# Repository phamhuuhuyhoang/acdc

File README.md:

# acdc

Power electronics toolbox

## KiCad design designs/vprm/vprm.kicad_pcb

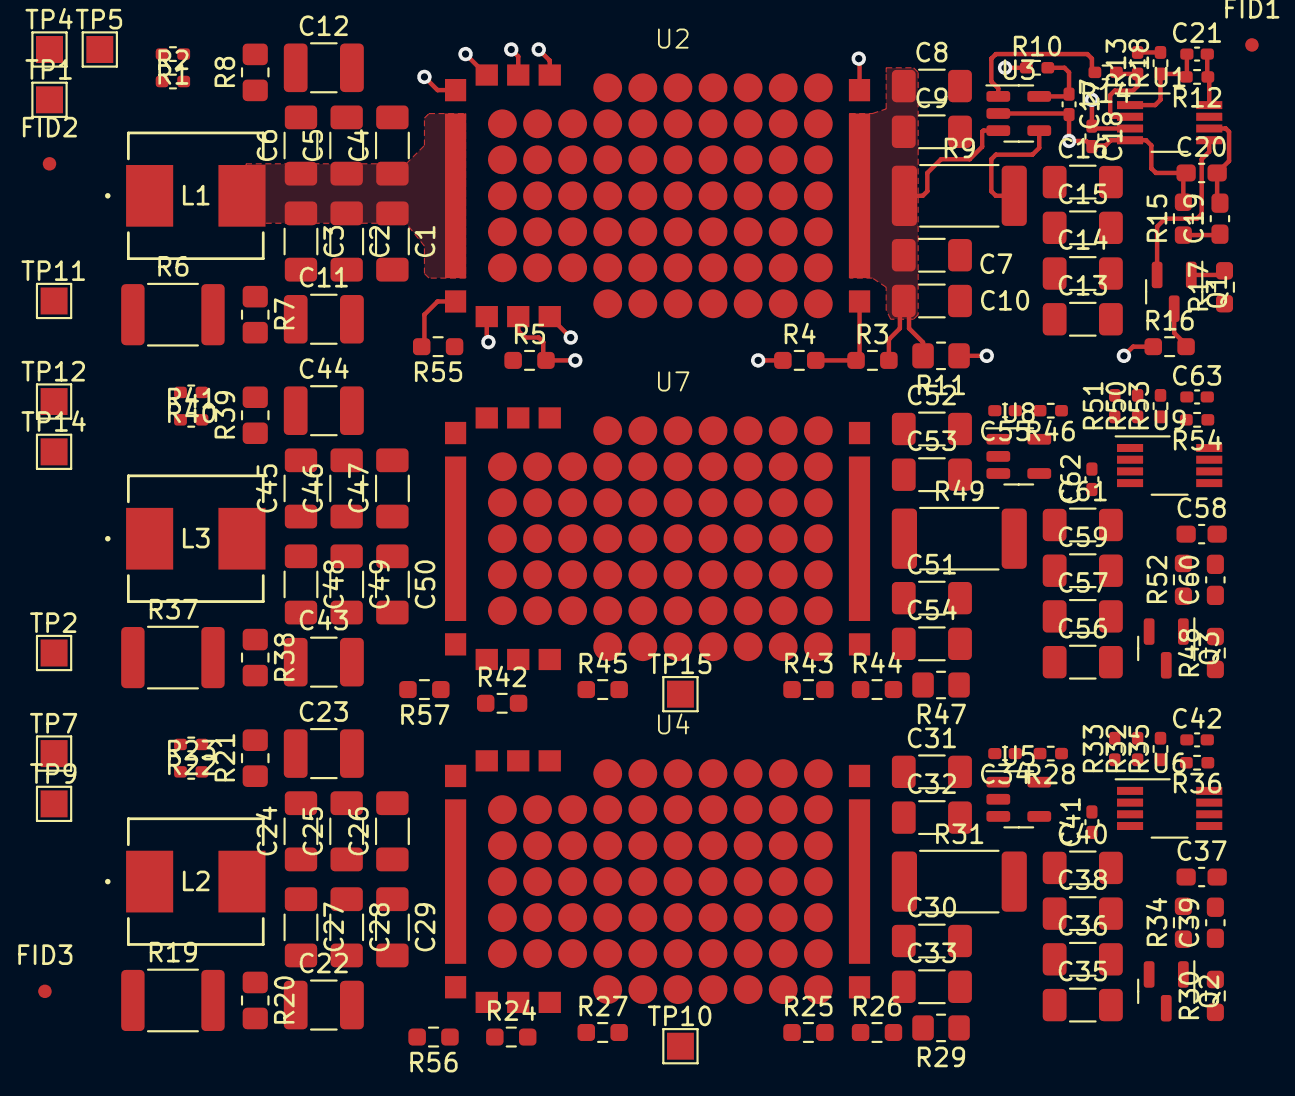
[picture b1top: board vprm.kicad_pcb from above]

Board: 8 copper layers, 150 parts (1 on the bottom side), 80 nets.

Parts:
C1, C2, C3, C4, C5, C6, C24, C25, C26, C27, C28, C29, C45, C46, C47, C48, C49, C50: C; C_1206_3216Metric_Pad1.33x1.80mm_HandSolder
C7, C8, C9, C10, C13, C14, C15, C16, C30, C31, C32, C33, C35, C36, C38, C40, C51, C52, C53, C54, C56, C57, C59, C61: 4.7uF; C_1206_3216Metric_Pad1.33x1.80mm_HandSolder
C11, C12, C22, C23, C43, C44: C; C_1210_3225Metric_Pad1.33x2.70mm_HandSolder
C17, C18, C21, C34, C41, C42, C55, C62, C63: 0.1uF; C_0402_1005Metric_Pad0.74x0.62mm_HandSolder
C19, C20, C37, C39, C58, C60: 0.1uF; C_0603_1608Metric_Pad1.08x0.95mm_HandSolder
FID1, FID2, FID3: Fiducial; Fiducial_0.75mm_Mask1.5mm
L1, L2, L3: L; IND_IHLP_2525_CZ_VIS-M
Q1, Q2, Q3: BC846; SOT-23
R1, R2, R22, R23, R40, R41: R; R_0402_1005Metric_Pad0.72x0.64mm_HandSolder
R3, R4, R5, R15, R16, R24, R25, R26, R27, R34, R42, R43, R44, R45, R52, R55, R56, R57: R; R_0603_1608Metric_Pad0.98x0.95mm_HandSolder
R6, R19, R37: R_US; R_1812_4532Metric_Pad1.30x3.40mm_HandSolder
R7, R8, R20, R21, R38, R39: R_US; R_0805_2012Metric_Pad1.20x1.40mm_HandSolder
R9, R31, R49: R; R_2512_6332Metric_Pad1.40x3.35mm_HandSolder
R10, R28, R46: 10; R_0402_1005Metric_Pad0.72x0.64mm_HandSolder
R11, R29, R47: 4k; R_0805_2012Metric_Pad1.20x1.40mm_HandSolder
R12, R13, R32, R36, R50, R54: 4k; R_0402_1005Metric_Pad0.72x0.64mm_HandSolder
R14, R18, R33, R35, R51, R53: 1k; R_0402_1005Metric_Pad0.72x0.64mm_HandSolder
R17, R30, R48: DNP; R_0603_1608Metric_Pad0.98x0.95mm_HandSolder
TP1, TP2, TP4, TP5, TP6, TP7, TP9, TP10, TP11, TP12, TP14, TP15: TestPoint; TestPoint_Pad_1.5x1.5mm
U1, U6, U9: UCC39002D; VSSOP-8_3.0x3.0mm_P0.65mm
U2, U4, U7: PRM2313; 2313 PRM TC2_3-47574R4
U3, U5, U8: AD8211; SOT-23-5

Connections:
/block1/5VCC: C17.1, R10.2, U3.5 (V+)
/block1/+IN: C1.1, C2.1, C3.1, C4.1, C5.1, C6.1, L1.2, R6.2, R7.1, R8.1, U2.11 (+IN)
/block1/+VS: R3.1, R4.2, U2.4 (+VS)
/block1/EAO: TP6.1, U2.3 (EAO)
/block1/IN_COM: L1.1, R6.1
/block1/ISNS: R14.2, U3.1 (OUT)
/block1/ITRIM: R55.2, U2.12 (ITRIM)
/block1/PG: TP1.1, U2.7 (PGOOD)
/block1/TR-ADJ: Q1.3 (C), R16.2
/block1/TRIM: R4.1, R5.2, R16.1, U2.2 (TRIM)
/block1/VDD: C18.1, Q1.1 (B), R11.1, R17.2, U1.3 (VDD)
/block1/VDR: R10.1, U2.6 (VDR)
/block1/VOUT: C7.1, C8.1, C9.1, C10.1, R3.2, R9.1, R11.2, U2.5 (+OUT), U3.3 (Vin+)
/block1/VOUT_COM: C13.1, C14.1, C15.1, C16.1, R9.2, U3.4 (Vin-)
/block2/5VCC: C34.1, R28.2, U5.5 (V+)
/block2/+IN: C24.1, C25.1, C26.1, C27.1, C28.1, C29.1, L2.2, R19.2, R20.1, R21.1, U4.11 (+IN)
/block2/+VS: R25.2, R26.1, U4.4 (+VS)
/block2/EAO: TP10.1, U4.3 (EAO)
/block2/IN_COM: L2.1, R19.1
/block2/ISNS: R33.2, U5.1 (OUT)
/block2/ITRIM: R56.2, U4.12 (ITRIM)
/block2/PG: TP9.1, U4.7 (PGOOD)
/block2/TR-ADJ: Q2.3 (C), R27.2
/block2/TRIM: R24.2, R25.1, R27.1, U4.2 (TRIM)
/block2/VDD: C41.1, Q2.1 (B), R29.1, R30.2, U6.3 (VDD)
/block2/VDR: R28.1, U4.6 (VDR)
/block2/VOUT: C30.1, C31.1, C32.1, C33.1, R26.2, R29.2, R31.1, U4.5 (+OUT), U5.3 (Vin+)
/block2/VOUT_COM: C35.1, C36.1, C38.1, C40.1, R31.2, U5.4 (Vin-)
/block3/5VCC: C55.1, R46.2, U8.5 (V+)
/block3/+IN: C45.1, C46.1, C47.1, C48.1, C49.1, C50.1, L3.2, R37.2, R38.1, R39.1, U7.11 (+IN)
/block3/+VS: R43.2, R44.1, U7.4 (+VS)
/block3/EAO: TP15.1, U7.3 (EAO)
/block3/IN_COM: L3.1, R37.1
/block3/ISNS: R51.2, U8.1 (OUT)
/block3/ITRIM: R57.2, U7.12 (ITRIM)
/block3/PG: TP14.1, U7.7 (PGOOD)
/block3/TR-ADJ: Q3.3 (C), R45.2
/block3/TRIM: R42.2, R43.1, R45.1, U7.2 (TRIM)
/block3/VDD: C62.1, Q3.1 (B), R47.1, R48.2, U9.3 (VDD)
/block3/VDR: R46.1, U7.6 (VDR)
/block3/VOUT: C51.1, C52.1, C53.1, C54.1, R44.2, R47.2, R49.1, U7.5 (+OUT), U8.3 (Vin+)
/block3/VOUT_COM: C56.1, C57.1, C59.1, C61.1, R49.2, U8.4 (Vin-)
GND: C1.2, C2.2, C3.2, C4.2, C5.2, C6.2, C7.2, C8.2, C9.2, C10.2, C11.2, C12.2, C13.2, C14.2, C15.2, C16.2, C22.2, C23.2, C24.2, C25.2, C26.2, C27.2, C28.2, C29.2, C30.2, C31.2, C32.2, C33.2, C35.2, C36.2, C38.2, C40.2, C43.2, C44.2, C45.2, C46.2, C47.2, C48.2, C49.2, C50.2, C51.2, C52.2, C53.2, C54.2, C56.2, C57.2, C59.2, C61.2, U2.13 (PGND), U4.13 (PGND), U7.13 (PGND)
unnamed: C11.1, R7.2
unnamed: C12.1, R8.2
unnamed: C19.1, R15.1
unnamed: C22.1, R20.2
unnamed: C23.1, R21.2
unnamed: C39.1, R34.1
unnamed: C43.1, R38.2
unnamed: C44.1, R39.2
unnamed: C60.1, R52.1
unnamed: Q1.2 (E), U1.5 (ADJ)
unnamed: Q2.2 (E), U6.5 (ADJ)
unnamed: Q3.2 (E), U9.5 (ADJ)
unnamed: R1.2, TP4.1
unnamed: R2.1, TP5.1
unnamed: R22.2, TP7.1
unnamed: R23.1, TP2.1
unnamed: R40.2, TP12.1
unnamed: R41.1, TP11.1
unnamed: R13.1, R14.1, U1.2 (CS+)
unnamed: C21.1, R12.2, R18.1, U1.1 (CS-)
unnamed: C21.2, R12.1, U1.8 (CSO)
unnamed: C19.2, C20.2, U1.6 (EAO)
unnamed: R1.1, U2.9 (SCL)
unnamed: R2.2, U2.10 (SDA)
unnamed: R22.1, U4.9 (SCL)
unnamed: R23.2, U4.10 (SDA)
unnamed: R32.1, R33.1, U6.2 (CS+)
unnamed: C42.1, R35.1, R36.2, U6.1 (CS-)
unnamed: C42.2, R36.1, U6.8 (CSO)
unnamed: C37.2, C39.2, U6.6 (EAO)
unnamed: R40.1, U7.9 (SCL)
unnamed: R41.2, U7.10 (SDA)
unnamed: R50.1, R51.1, U9.2 (CS+)
unnamed: C63.1, R53.1, R54.2, U9.1 (CS-)
unnamed: C63.2, R54.1, U9.8 (CSO)
unnamed: C58.2, C60.2, U9.6 (EAO)
SGND: C17.2, C18.2, C20.1, C34.2, C37.1, C41.2, C55.2, C58.1, C62.2, R5.1, R13.2, R15.2, R17.1, R18.2, R24.1, R30.1, R32.2, R34.2, R35.2, R42.1, R48.1, R50.2, R52.2, R53.2, R55.1, R56.1, R57.1, U1.4 (GND), U2.1 (SGND), U3.2 (GND), U4.1 (SGND), U5.2 (GND), U6.4 (GND), U7.1 (SGND), U8.2 (GND), U9.4 (GND)

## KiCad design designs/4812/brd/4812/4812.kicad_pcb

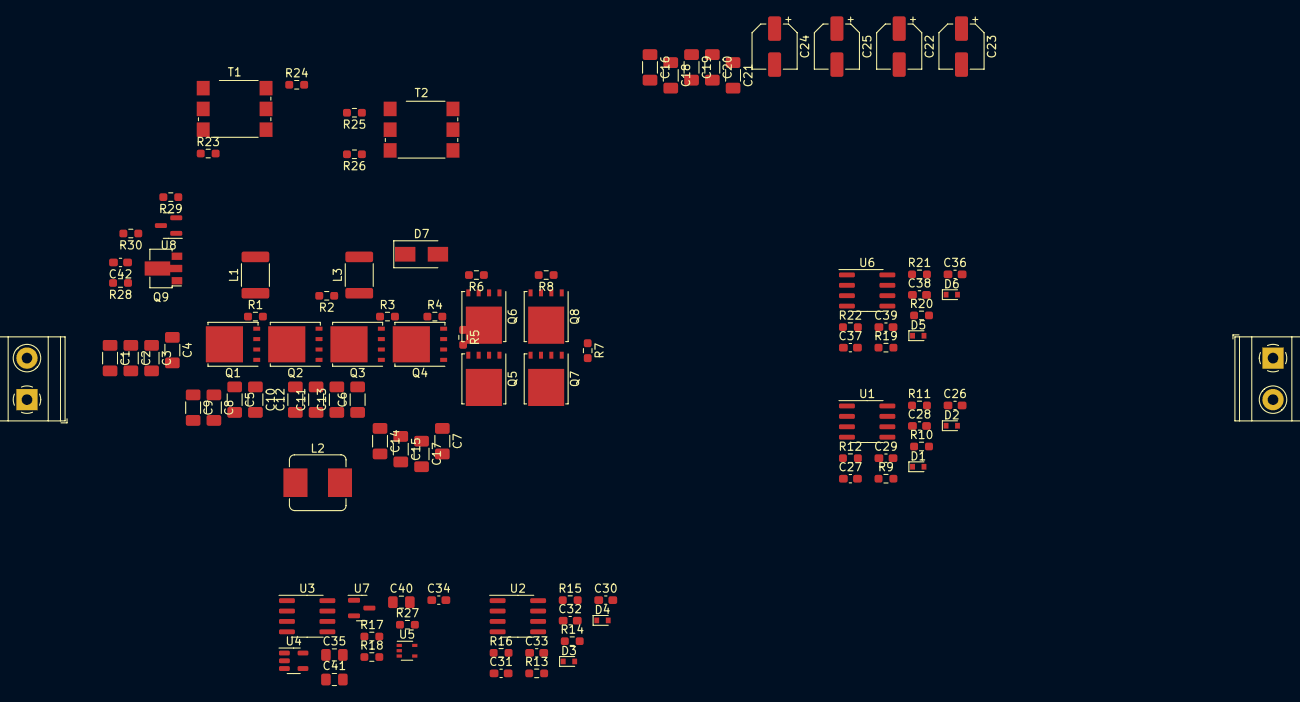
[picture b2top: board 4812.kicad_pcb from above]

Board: 2 copper layers, 103 parts (0 on the bottom side), 49 nets, no tracks yet.

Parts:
C1, C2, C3, C4: 2.2uF; C_1206_3216Metric_Pad1.33x1.80mm_HandSolder
C5, C6, C7, C8, C9, C10, C11, C12, C13, C14, C15, C17: 3.3uF; C_1206_3216Metric_Pad1.33x1.80mm_HandSolder
C16, C18, C19, C20, C21: 22uF; C_1206_3216Metric_Pad1.33x1.80mm_HandSolder
C22, C23, C24, C25: 47uF; CP_Elec_5x5.3
C26, C27, C30, C31, C36, C37: 100pF; C_0603_1608Metric_Pad1.08x0.95mm_HandSolder
C28, C32, C34, C38: 0.1uF; C_0603_1608Metric_Pad1.08x0.95mm_HandSolder
C29, C33, C39: 0.22uF; C_0603_1608Metric_Pad1.08x0.95mm_HandSolder
C35: 1200pF; C_0805_2012Metric_Pad1.18x1.45mm_HandSolder
C40, C41: 0.1uF; C_0805_2012Metric_Pad1.18x1.45mm_HandSolder
C42: 0.1u; C_0603_1608Metric_Pad1.08x0.95mm_HandSolder
D1, D2, D3, D4, D5, D6: 1N4148WT; D_SOD-523
D7: US1A; D_SMA
J1, J2: Screw_Terminal_01x02; TerminalBlock_Phoenix_MKDS-1,5-2-5.08_1x02_P5.08mm_Horizont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
L1, L3: 47nH; L_1812_4532Metric_Pad1.30x3.40mm_HandSolder
L2: 470nH; L_Bourns_SRP7028A_7.3x6.6mm
Q1, Q2, Q3, Q4: CSD18531Q5A; TDSON-8-1
Q5, Q6, Q7, Q8: CSD17305Q5A; TDSON-8-1
Q9: BCX56; SOT-89-3
R1, R2, R3, R4, R5, R6, R7, R8, R18: 4.99k; R_0603_1608Metric_Pad0.98x0.95mm_HandSolder
R9, R10, R13, R14, R19, R20: 100; R_0603_1608Metric_Pad0.98x0.95mm_HandSolder
R11, R12, R15, R16, R21, R22: 2; R_0603_1608Metric_Pad0.98x0.95mm_HandSolder
R17, R29: 1k; R_0603_1608Metric_Pad0.98x0.95mm_HandSolder
R23, R24, R25, R26: R0603; R_0603_1608Metric_Pad0.98x0.95mm_HandSolder
R27: 49.9k; R_0603_1608Metric_Pad0.98x0.95mm_HandSolder
R28: 22k; R_0603_1608Metric_Pad0.98x0.95mm_HandSolder
R30: 3k; R_0603_1608Metric_Pad0.98x0.95mm_HandSolder
T1, T2: PA0264NL; Pulse_PA2004NL
U1, U2, U6: HIP2101_SOIC; SOIC-8_3.9x4.9mm_P1.27mm
U3: LMC555xM; SOIC-8_3.9x4.9mm_P1.27mm
U4: NC7SZ125M5X; SOT-23-5
U5: NC7SVU04P5X; SOT-353_SC-70-5
U7: LM3480-5.0; SOT-23
U8: TL431DBZ; SOT-23

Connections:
+12V: C28.1, C32.1, C40.1, C42.1, D7.1 (K), Q9.3 (E), R30.2, U1.1 (VDD), U2.1 (VDD), U7.2 (VI)
/C1: C5.1, C8.1, C9.1, C10.1, L1.2
/C3: C7.1, C14.1, C15.1, C17.1, L3.2
/D: D1.1 (K), D3.1 (K), D6.1 (K), R9.1, R13.1, R20.1, U4.4 (Y)
/DN: D2.1 (K), D4.1 (K), D5.1 (K), R10.1, R14.1, R19.1, U5.4
/G1: Q1.4 (G), R1.1, R23.2
/G2: Q2.4 (G), R2.1, R24.2
/G3: Q3.4 (G), R3.1, R25.2
/G4: Q4.4 (G), R4.1, R26.2
/G5: Q5.4 (G), R5.2, R11.2
/G6: Q6.4 (G), R6.2, R12.2
/G7: Q7.4 (G), R7.2, R21.2
/G8: Q8.4 (G), R8.2, R22.2
/IN: C1.1, C2.1, C3.1, C4.1, J1.2, Q1.5 (D), Q9.2 (C), R28.1
/OUT: C16.1, C18.1, C19.1, C20.1, C21.1, C22.1, C23.1, C24.1, C25.1, D7.2 (A), J2.1, Q4.1 (S), Q4.2 (S), Q4.3 (S), Q5.5 (D), Q7.5 (D), R4.2, T2.3
/SW1: L1.1, Q1.1 (S), Q1.2 (S), Q1.3 (S), Q2.5 (D), R1.2, T1.5
/SW2: C6.1, C11.1, C12.1, C13.1, Q2.1 (S), Q2.2 (S), Q2.3 (S), Q3.5 (D), R2.2, T1.3
/SW3: L3.1, Q3.1 (S), Q3.2 (S), Q3.3 (S), Q4.5 (D), R3.2, T2.5
/SW4: C5.2, C7.2, C8.2, C9.2, C10.2, C14.2, C15.2, C17.2, C29.2, L2.1, Q5.1 (S), Q5.2 (S), Q5.3 (S), Q6.5 (D), R5.1, U1.4 (HS)
/SW5: C6.2, C11.2, C12.2, C13.2, C39.2, L2.2, Q7.1 (S), Q7.2 (S), Q7.3 (S), Q8.5 (D), R7.1, U6.4 (HS)
/ctrl/Q: R17.2, U3.3 (Q), U4.2 (A), U5.2
/ctrl/THR: C35.1, R17.1, U3.2 (TR), U3.6 (THR)
/hbdrv1/drvh: R15.2, T1.1, T2.1
/hbdrv1/drvl: R16.2, T1.6, T2.6
GND: C1.2, C2.2, C3.2, C4.2, C16.2, C18.2, C19.2, C20.2, C21.2, C22.2, C23.2, C24.2, C25.2, C26.2, C27.2, C28.2, C30.2, C31.2, C32.2, C33.2, C34.1, C35.2, C36.2, C37.2, C38.2, C40.2, C41.2, C42.2, J1.1, J2.2, Q6.1 (S), Q6.2 (S), Q6.3 (S), Q8.1 (S), Q8.2 (S), Q8.3 (S), R6.1, R8.1, R27.1, R29.2, U1.7 (VSS), U2.4 (HS), U2.7 (VSS), U3.1 (GND), U4.1 (~OE), U4.3 (GND), U5.3 (GND), U6.7 (VSS), U7.3 (GND), U8.3 (A)
unnamed: C26.1, D1.2 (A), R9.2, U1.5 (HI)
unnamed: C27.1, D2.2 (A), R10.2, U1.6 (LI)
unnamed: C29.1, U1.2 (HB)
unnamed: C30.1, D3.2 (A), R13.2, U2.5 (HI)
unnamed: C31.1, D4.2 (A), R14.2, U2.6 (LI)
unnamed: C33.1, U2.2 (HB)
unnamed: C36.1, D5.2 (A), R19.2, U6.5 (HI)
unnamed: C37.1, D6.2 (A), R20.2, U6.6 (LI)
unnamed: C39.1, U6.2 (HB)
unnamed: Q9.1 (B), R28.2, U8.1 (K)
unnamed: R11.1, U1.3 (HO)
unnamed: R12.1, U1.8 (LO)
unnamed: R15.1, U2.3 (HO)
unnamed: R16.1, U2.8 (LO)
unnamed: R18.1, U3.7 (DIS)
unnamed: R21.1, U6.3 (HO)
unnamed: R22.1, U6.8 (LO)
unnamed: R23.1, T1.2
unnamed: R25.1, T2.2
unnamed: R29.1, R30.1, U8.2 (REF)
unnamed: R24.1, T1.4
unnamed: R26.1, T2.4
unnamed: R27.2, U3.5 (CV)
VDD: C34.2, C38.1, C41.1, R18.2, U3.4 (R), U3.8 (VCC), U4.5 (VCC), U5.5 (VCC), U6.1 (VDD), U7.1 (VO)

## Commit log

2022-08-06 pwm tools
    added simulation scaffolding blocks:
    pulse width modulator
    half bridge driver
2022-08-13 added 4812 scr sim
    Added a simulation model for a 48 to 12 switch cap resonant converter
2022-08-16 added schematic
    added kicad schematic and started layout
2022-12-08 added test jigs
    added test jigs and average model of forward topology
2023-09-28 added parameters for dead time, rise time, and amplitude
2023-10-31 added simulation file for 48V PSU and BBU
2023-10-31 added 48V simulations
2024-06-15 added pcie_breakout design
2024-06-15 added vprm design
